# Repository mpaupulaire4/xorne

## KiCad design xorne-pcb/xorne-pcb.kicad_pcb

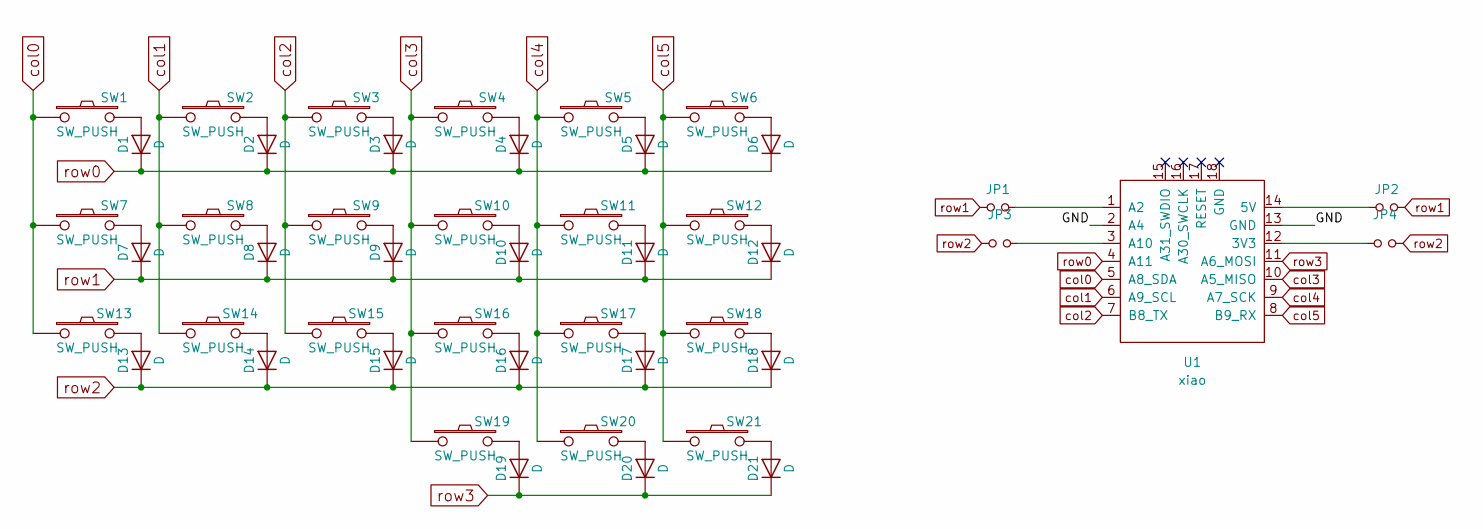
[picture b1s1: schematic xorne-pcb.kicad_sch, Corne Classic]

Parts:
D1, D2, D3, D4, D5, D6, D7, D8, D9, D10, D11, D12, D13, D14, D15, D16, D17, D18, D19, D20, D21: D; D3_SMD
JP1, JP2, JP3, JP4: Jumper_NO_Small-Device; Jumper
SW1, SW2, SW3, SW4, SW5, SW6, SW7, SW8, SW9, SW10, SW11, SW12, SW13, SW14, SW15, SW16, SW17, SW18, SW19, SW20, SW21: SW_PUSH; SW_Kailh_Choc_Mini_2
U1: xiao; xiao-tht

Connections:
/GND: U1.2 (A4), U1.13 (GND)
unnamed: D1.2 (A), SW1.2
unnamed: D2.2 (A), SW2.2
unnamed: D3.2 (A), SW3.2
unnamed: D4.2 (A), SW4.2
unnamed: D5.2 (A), SW5.2
unnamed: D6.2 (A), SW6.2
unnamed: D7.2 (A), SW7.2
unnamed: D8.2 (A), SW8.2
unnamed: D9.2 (A), SW9.2
unnamed: D10.2 (A), SW10.2
unnamed: D11.2 (A), SW11.2
unnamed: D12.2 (A), SW12.2
unnamed: D13.2 (A), SW13.2
unnamed: D14.2 (A), SW14.2
unnamed: D15.2 (A), SW15.2
unnamed: D16.2 (A), SW16.2
unnamed: D17.2 (A), SW17.2
unnamed: D18.2 (A), SW18.2
unnamed: D19.2 (A), SW19.2
unnamed: D20.2 (A), SW20.2
unnamed: D21.2 (A), SW21.2
unnamed: JP1.1, U1.1 (A2)
unnamed: JP2.1, U1.14 (5V)
unnamed: JP3.1, U1.3 (A10)
unnamed: JP4.1, U1.12 (3V3)
col0: SW1.1, SW7.1, SW13.1, U1.5 (A8_SDA)
col1: SW2.1, SW8.1, SW14.1, U1.6 (A9_SCL)
col2: SW3.1, SW9.1, SW15.1, U1.7 (B8_TX)
col3: SW4.1, SW10.1, SW16.1, SW19.1, U1.10 (A5_MISO)
col4: SW5.1, SW11.1, SW17.1, SW20.1, U1.9 (A7_SCK)
col5: SW6.1, SW12.1, SW18.1, SW21.1, U1.8 (B9_RX)
row0: D1.1 (K), D2.1 (K), D3.1 (K), D4.1 (K), D5.1 (K), D6.1 (K), U1.4 (A11)
row1: D7.1 (K), D8.1 (K), D9.1 (K), D10.1 (K), D11.1 (K), D12.1 (K), JP1.2, JP2.2
row2: D13.1 (K), D14.1 (K), D15.1 (K), D16.1 (K), D17.1 (K), D18.1 (K), JP3.2, JP4.2
row3: D19.1 (K), D20.1 (K), D21.1 (K), U1.11 (A6_MOSI)

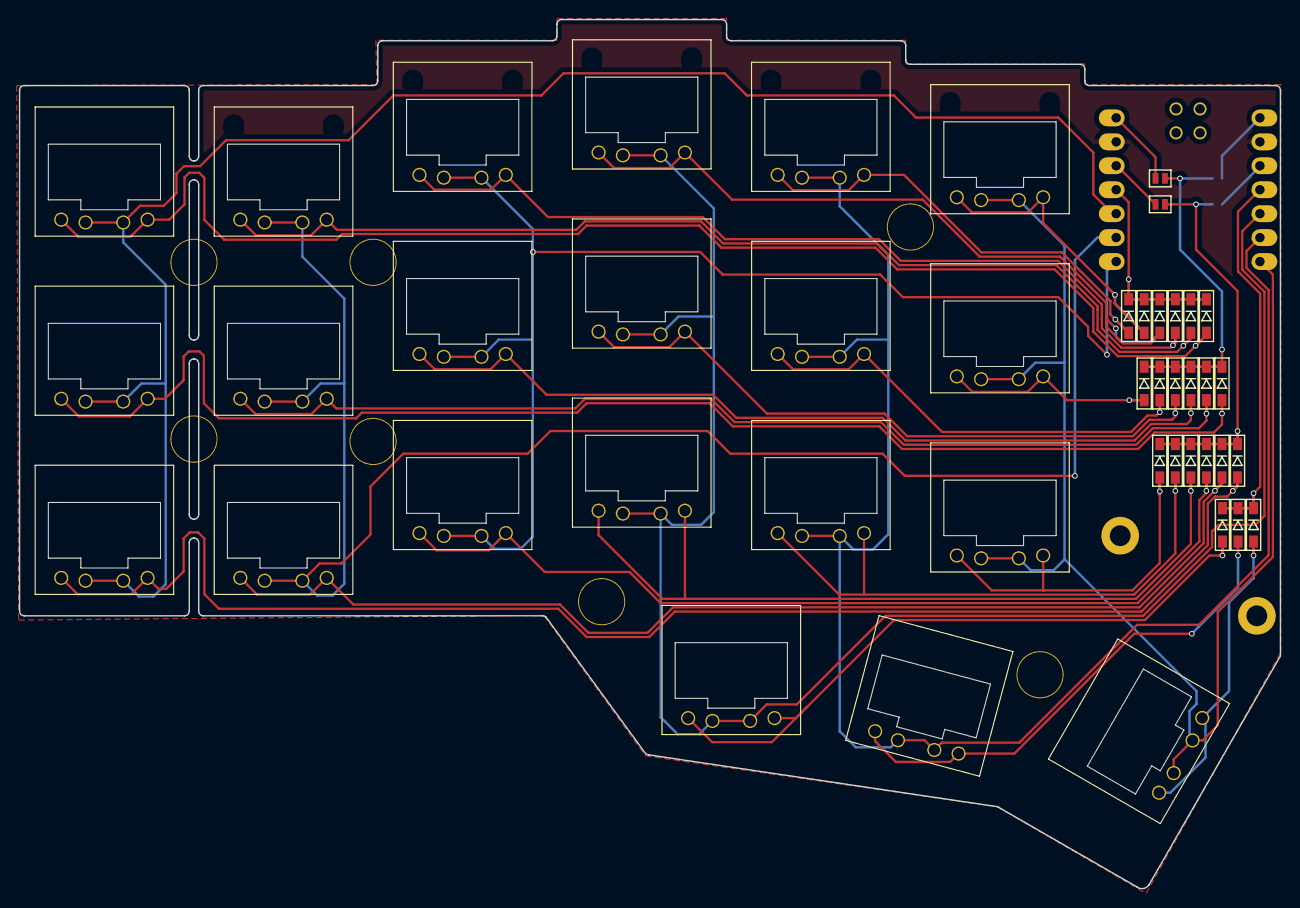
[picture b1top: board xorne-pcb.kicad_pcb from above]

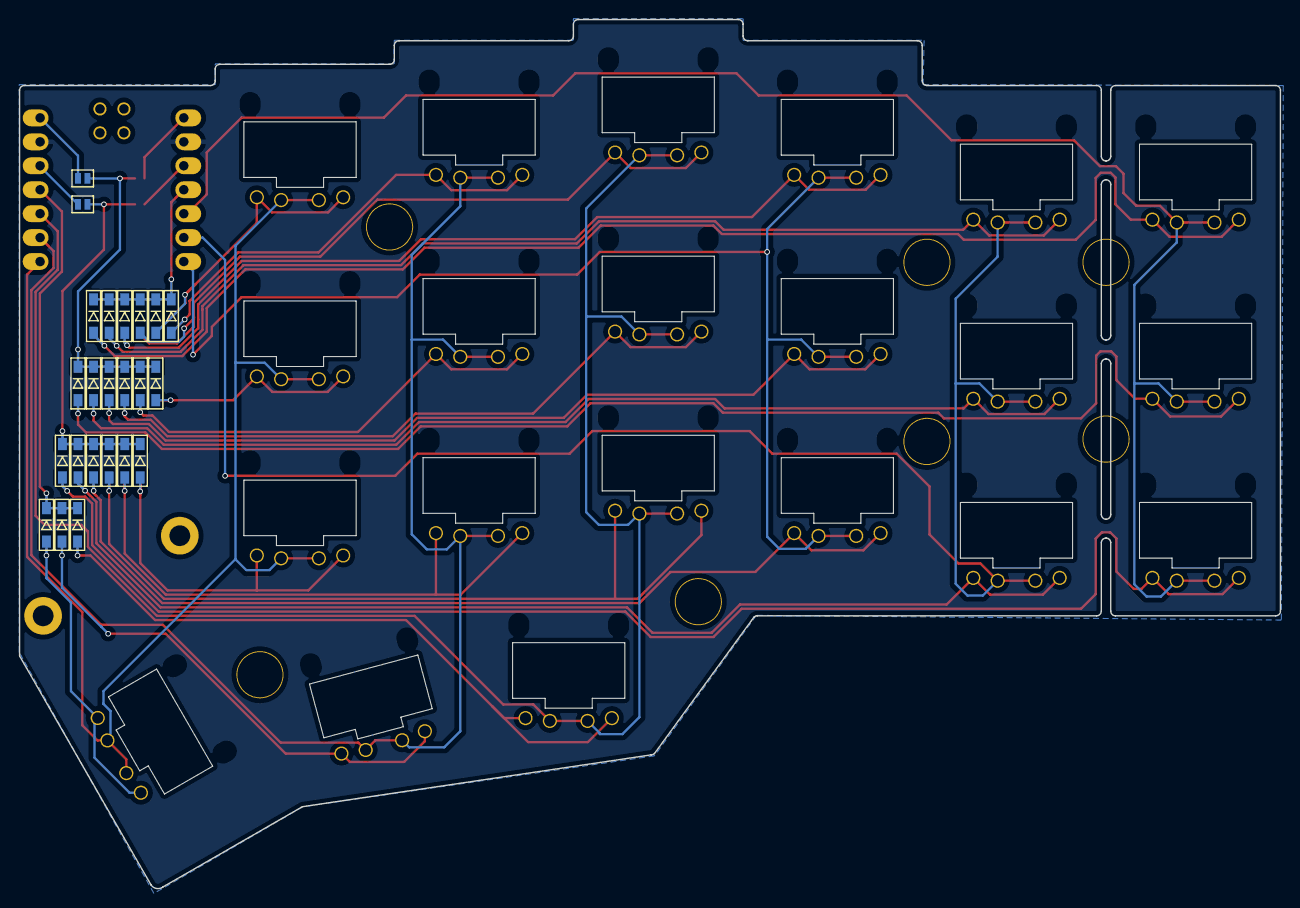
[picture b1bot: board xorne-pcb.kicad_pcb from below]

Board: 2 copper layers, 133.8 x 92.2 mm, 47 parts (2 on the bottom side), 36 nets.

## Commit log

2022-12-12 initial with rename
2022-12-14 save progress
2022-12-24 save pin changes
2022-12-24 change board
2022-12-24 metadata
2022-12-24 reverse columns
